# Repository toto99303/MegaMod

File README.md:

# MegaMod
These are the three versions of MegaMod PCB for Sega Genesis.
Created with Eagle PCB.

v1 - uses PIC16F630 (https://vmod.wordpress.com/megamod-v1-0/)  
v2 - uses Atmega328P with internal oscillator (https://vmod.wordpress.com/megamod-v2-0/)  
v3 - uses Atmega328P with internal oscillator + THS video amp (https://vmod.wordpress.com/megamod-v3-0/)

PIC code used in v1: https://github.com/sebknzl/saturnmod

The Arduino code for v2 and v3 was based on this project:
https://github.com/SukkoPera/MegaDrivePlusPlus

Due to some bugs related to the Atmega328P internal oscillator the Arduino code was never finished.

The audio part of the mod is based on the circuits posted in this forum by Ace (MegaAmp):
http://www.sega-16.com/forum/showthread.php?26568-Introducing-the-Mega-Amp-The-universal-Genesis-audio-circuit

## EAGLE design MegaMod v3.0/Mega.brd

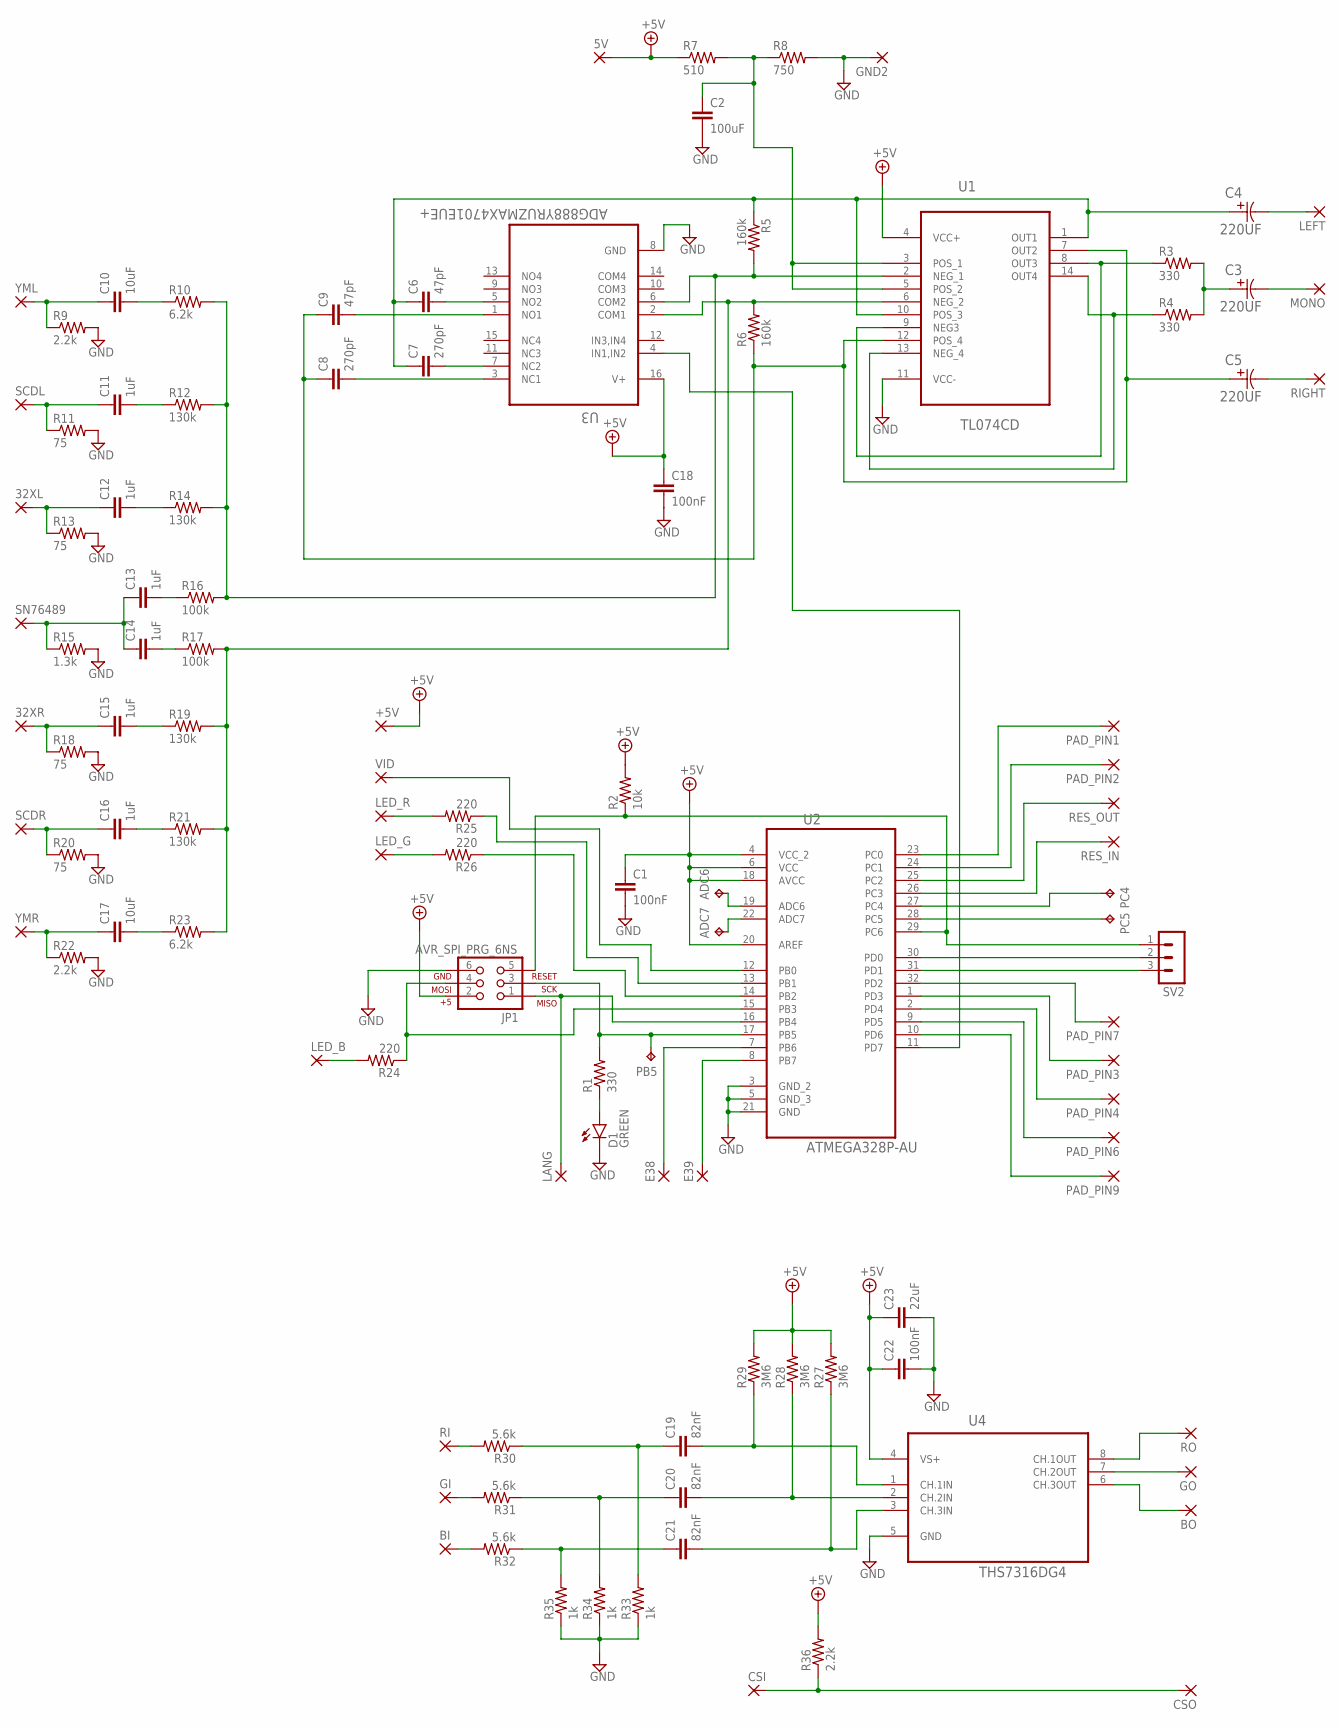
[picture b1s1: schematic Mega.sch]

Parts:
5V, 32XL, 32XR: SMD2; SMD1,27-2,54
+5V: SMD2; SMD1,27-2,54
ADC6, ADC7: TPB1,27; B1,27
BI: SMD2; SMD1,27-2,54
BO: SMD2; SMD1,27-2,54
C1, C18, C22: 100nF; 0805
C2: 100uF; 1206
C3, C4, C5: 220UF; CAPAE830X650N; TOLERANCE 20 %
C6, C9: 47pF; 0805
C7, C8: 270pF; 0805
C10, C17: 10uF; 0805
C11, C12, C13, C14, C15, C16: 1uF; 0805
C19, C20, C21: 82nF; 0805
C23: 22uF; 0805
CSI: SMD2; SMD1,27-2,54
CSO: SMD2; SMD1,27-2,54
D1: GREEN; LED-1206
E38, E39: SMD2; SMD1,27-2,54
GI: SMD2; SMD1,27-2,54
GND2: SMD2; SMD1,27-2,54
GO: SMD2; SMD1,27-2,54
JP1: AVR_SPI_PRG_6NS; 2X3-NS
LANG: SMD2; SMD1,27-2,54
LED_B: SMD2; SMD1,27-2,54
LED_G: SMD2; SMD1,27-2,54
LED_R: SMD2; SMD1,27-2,54
LEFT: SMD2; SMD1,27-2,54
MONO: SMD2; SMD1,27-2,54
PAD_PIN1, PAD_PIN2, PAD_PIN3, PAD_PIN4, PAD_PIN6, PAD_PIN7, PAD_PIN9: SMD2; SMD1,27-2,54
PB5: TPB1,27; B1,27
PC4, PC5: TPB1,27; B1,27
R1, R3, R4: 330; 0805
R2: 10k; 0805
R5, R6: 160k; 0805
R7: 510; 0805
R8: 750; 0805
R9, R22, R36: 2.2k; 0805
R10, R23: 6.2k; 0805
R11, R13, R18, R20: 75; 0805
R12, R14, R19, R21: 130k; 0805
R15: 1.3k; 0805
R16, R17: 100k; 0805
R24, R25, R26: 220; 0805
R27, R28, R29: 3M6; 0805
R30, R31, R32: 5.6k; 0805
R33, R34, R35: 1k; 0805
RES_IN: SMD2; SMD1,27-2,54
RES_OUT: SMD2; SMD1,27-2,54
RI: SMD2; SMD1,27-2,54
RIGHT: SMD2; SMD1,27-2,54
RO: SMD2; SMD1,27-2,54
SCDL: SMD2; SMD1,27-2,54
SCDR: SMD2; SMD1,27-2,54
SN76489: SMD2; SMD1,27-2,54
SV2: MA03-1
U1: TL074CD; SOIC127P600X175-14N
U2: ATMEGA328P-AU; QFP80P900X900X120-32N
U3: ADG888YRUZMAX4701EUE+; SOP65P640X120-16N
U4: THS7316DG4; SOIC127P600X175-8N
VID: SMD2; SMD1,27-2,54
YML: SMD2; SMD1,27-2,54
YMR: SMD2; SMD1,27-2,54

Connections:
+5V: 5V.1, +5V.1, C1.1, C18.1, C22.1, C23.1, JP1.2, R2.2, R7.1, R27.2, R28.2, R29.2, R36.2, U1.4 (VCC+), U2.4 (VCC_2), U2.6 (VCC), U2.18 (AVCC), U2.20 (AREF), U3.16 (V+), U4.4 (VS+)
GND: C1.2, C2.2, C18.2, C22.2, C23.2, D1.C, GND2.1, JP1.6, R8.2, R9.2, R11.2, R13.2, R15.2, R18.2, R20.2, R22.2, R33.1, R34.1, R35.1, U1.11 (VCC-), U2.3 (GND_2), U2.5 (GND_3), U2.21 (GND), U3.8 (GND), U4.5 (GND)
unnamed: D1.A, R1.1
unnamed: JP1.3, PB5.TP, R1.2, U2.17 (PB5)
unnamed: JP1.5, R2.1, SV2.1, U2.29 (PC6)
unnamed: JP1.1, LANG.1, U2.16 (PB4)
unnamed: JP1.4, R24.1, U2.15 (PB3)
unnamed: LED_R.1, R25.2
unnamed: LED_G.1, R26.2
unnamed: R3.1, U1.8 (OUT3), U1.9 (NEG3)
unnamed: PC4.TP, U2.27 (PC4)
unnamed: PC5.TP, U2.28 (PC5)
unnamed: R4.1, U1.13 (NEG_4), U1.14 (OUT4)
unnamed: C3.1, R3.2, R4.2
unnamed: C3.2, MONO.1
unnamed: C4.2, LEFT.1
unnamed: RES_IN.1, U2.26 (PC3)
unnamed: C4.1, C6.1, C7.1, R5.1, U1.1 (OUT1), U1.10 (POS_3)
unnamed: C5.1, C8.1, C9.1, R6.1, U1.7 (OUT2), U1.12 (POS_4)
unnamed: C5.2, RIGHT.1
unnamed: R6.2, R17.2, R19.2, R21.2, R23.2, U1.6 (NEG_2), U3.2 (COM1)
unnamed: C6.2, U3.5 (NO2)
unnamed: C8.2, U3.3 (NC1)
unnamed: C7.2, U3.7 (NC2)
unnamed: C9.2, U3.1 (NO1)
unnamed: C10.1, R9.1, YML.1
unnamed: C2.1, R7.2, R8.1, U1.3 (POS_1), U1.5 (POS_2)
unnamed: C10.2, R10.1
unnamed: C11.1, R11.1, SCDL.1
unnamed: C11.2, R12.1
unnamed: 32XL.1, C12.1, R13.1
unnamed: C12.2, R14.1
unnamed: C13.1, C14.1, R15.1, SN76489.1
unnamed: C13.2, R16.1
unnamed: C17.1, R22.1, YMR.1
unnamed: C14.2, R17.1
unnamed: 32XR.1, C15.1, R18.1
unnamed: C15.2, R19.1
unnamed: C16.1, R20.1, SCDR.1
unnamed: C16.2, R21.1
unnamed: C17.2, R23.1
unnamed: R5.2, R10.2, R12.2, R14.2, R16.2, U1.2 (NEG_1), U3.6 (COM2)
unnamed: PAD_PIN2.1, U2.24 (PC1)
unnamed: SV2.3, U2.31 (PD1)
unnamed: SV2.2, U2.30 (PD0)
unnamed: PAD_PIN7.1, U2.32 (PD2)
unnamed: PAD_PIN3.1, U2.1 (PD3)
unnamed: PAD_PIN4.1, U2.2 (PD4)
unnamed: PAD_PIN6.1, U2.9 (PD5)
unnamed: PAD_PIN9.1, U2.10 (PD6)
unnamed: LED_B.1, R24.2
unnamed: R26.1, U2.14 (PB2)
unnamed: R25.1, U2.13 (PB1)
unnamed: U2.12 (PB0), VID.1
unnamed: E38.1, U2.7 (PB6)
unnamed: E39.1, U2.8 (PB7)
unnamed: U2.11 (PD7), U3.4 (IN1,IN2)
unnamed: C20.2, R28.1, U4.2 (CH.2IN)
unnamed: C19.2, R29.1, U4.1 (CH.1IN)
unnamed: C21.2, R27.1, U4.3 (CH.3IN)
unnamed: C19.1, R30.1, R33.2
unnamed: C20.1, R31.1, R34.2
unnamed: C21.1, R32.1, R35.2
unnamed: BI.1, R32.2
unnamed: GI.1, R31.2
unnamed: R30.2, RI.1
unnamed: CSI.1, CSO.1, R36.1
unnamed: GO.1, U4.7 (CH.2OUT)
unnamed: RO.1, U4.8 (CH.1OUT)
unnamed: BO.1, U4.6 (CH.3OUT)
unnamed: RES_OUT.1, U2.25 (PC2)
unnamed: PAD_PIN1.1, U2.23 (PC0)
unnamed: ADC7.TP, U2.22 (ADC7)
unnamed: ADC6.TP, U2.19 (ADC6)

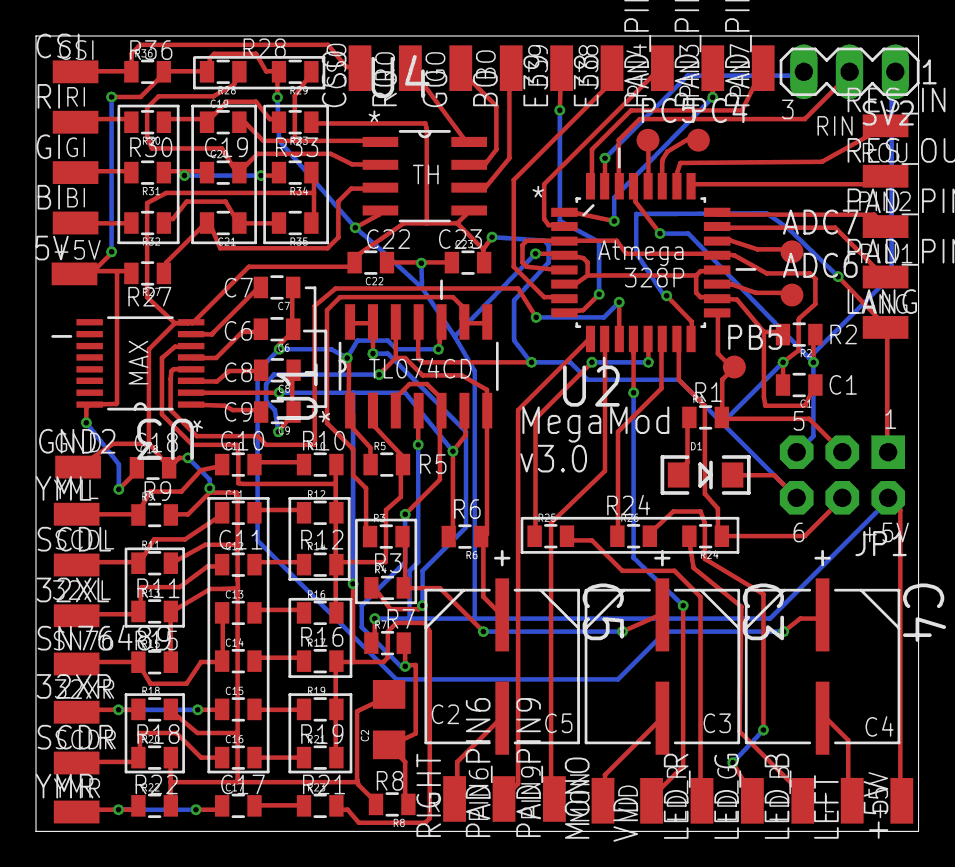
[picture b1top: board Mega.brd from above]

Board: 2 copper layers, 49.0 x 44.2 mm, 108 parts (0 on the bottom side), 74 nets.

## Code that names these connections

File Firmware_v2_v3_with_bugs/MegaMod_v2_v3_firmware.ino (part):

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void select_low() {
	// Select is low, we have Start & A
	byte portdd = PIND;
	pad_status = (pad_status & 0x3F) | ((~portdd & ((1 << PD6) | (1 << PD5))) << 1);
 // delayMicroseconds(15000);
}

inline byte read_pad () {

    // Update UP and DOWN, which are always valid and on PORTC alone
    pad_status = (pad_status & 0xFC) | (~PINC & ((1 << PC1) | (1 << PC0)));

    byte portd = PIND;
    // Select is high, we have Right, Left, C & B
    pad_status = (pad_status & 0xC3) | ((~portd & ((1 << PIND6) | (1 << PD5) | (1 << PD4) | (1 << PD3))) >> 1);
    
    return pad_status;
}
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
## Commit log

2019-03-19 Create test
2019-03-19 Create a
2019-03-23 Create a
    a

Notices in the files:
parts and their libraries:
SparkFun-Capacitors: Licensing: Creative Commons ShareAlike 4.0 International - https://creativecommons.org/licenses/by-sa/4.0
